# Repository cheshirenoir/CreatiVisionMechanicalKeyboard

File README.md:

CreatiVision Mechanical Keyboard
Untested (as yet. It's about $100 in parts!)
CC BY SA
Made in KiCAD

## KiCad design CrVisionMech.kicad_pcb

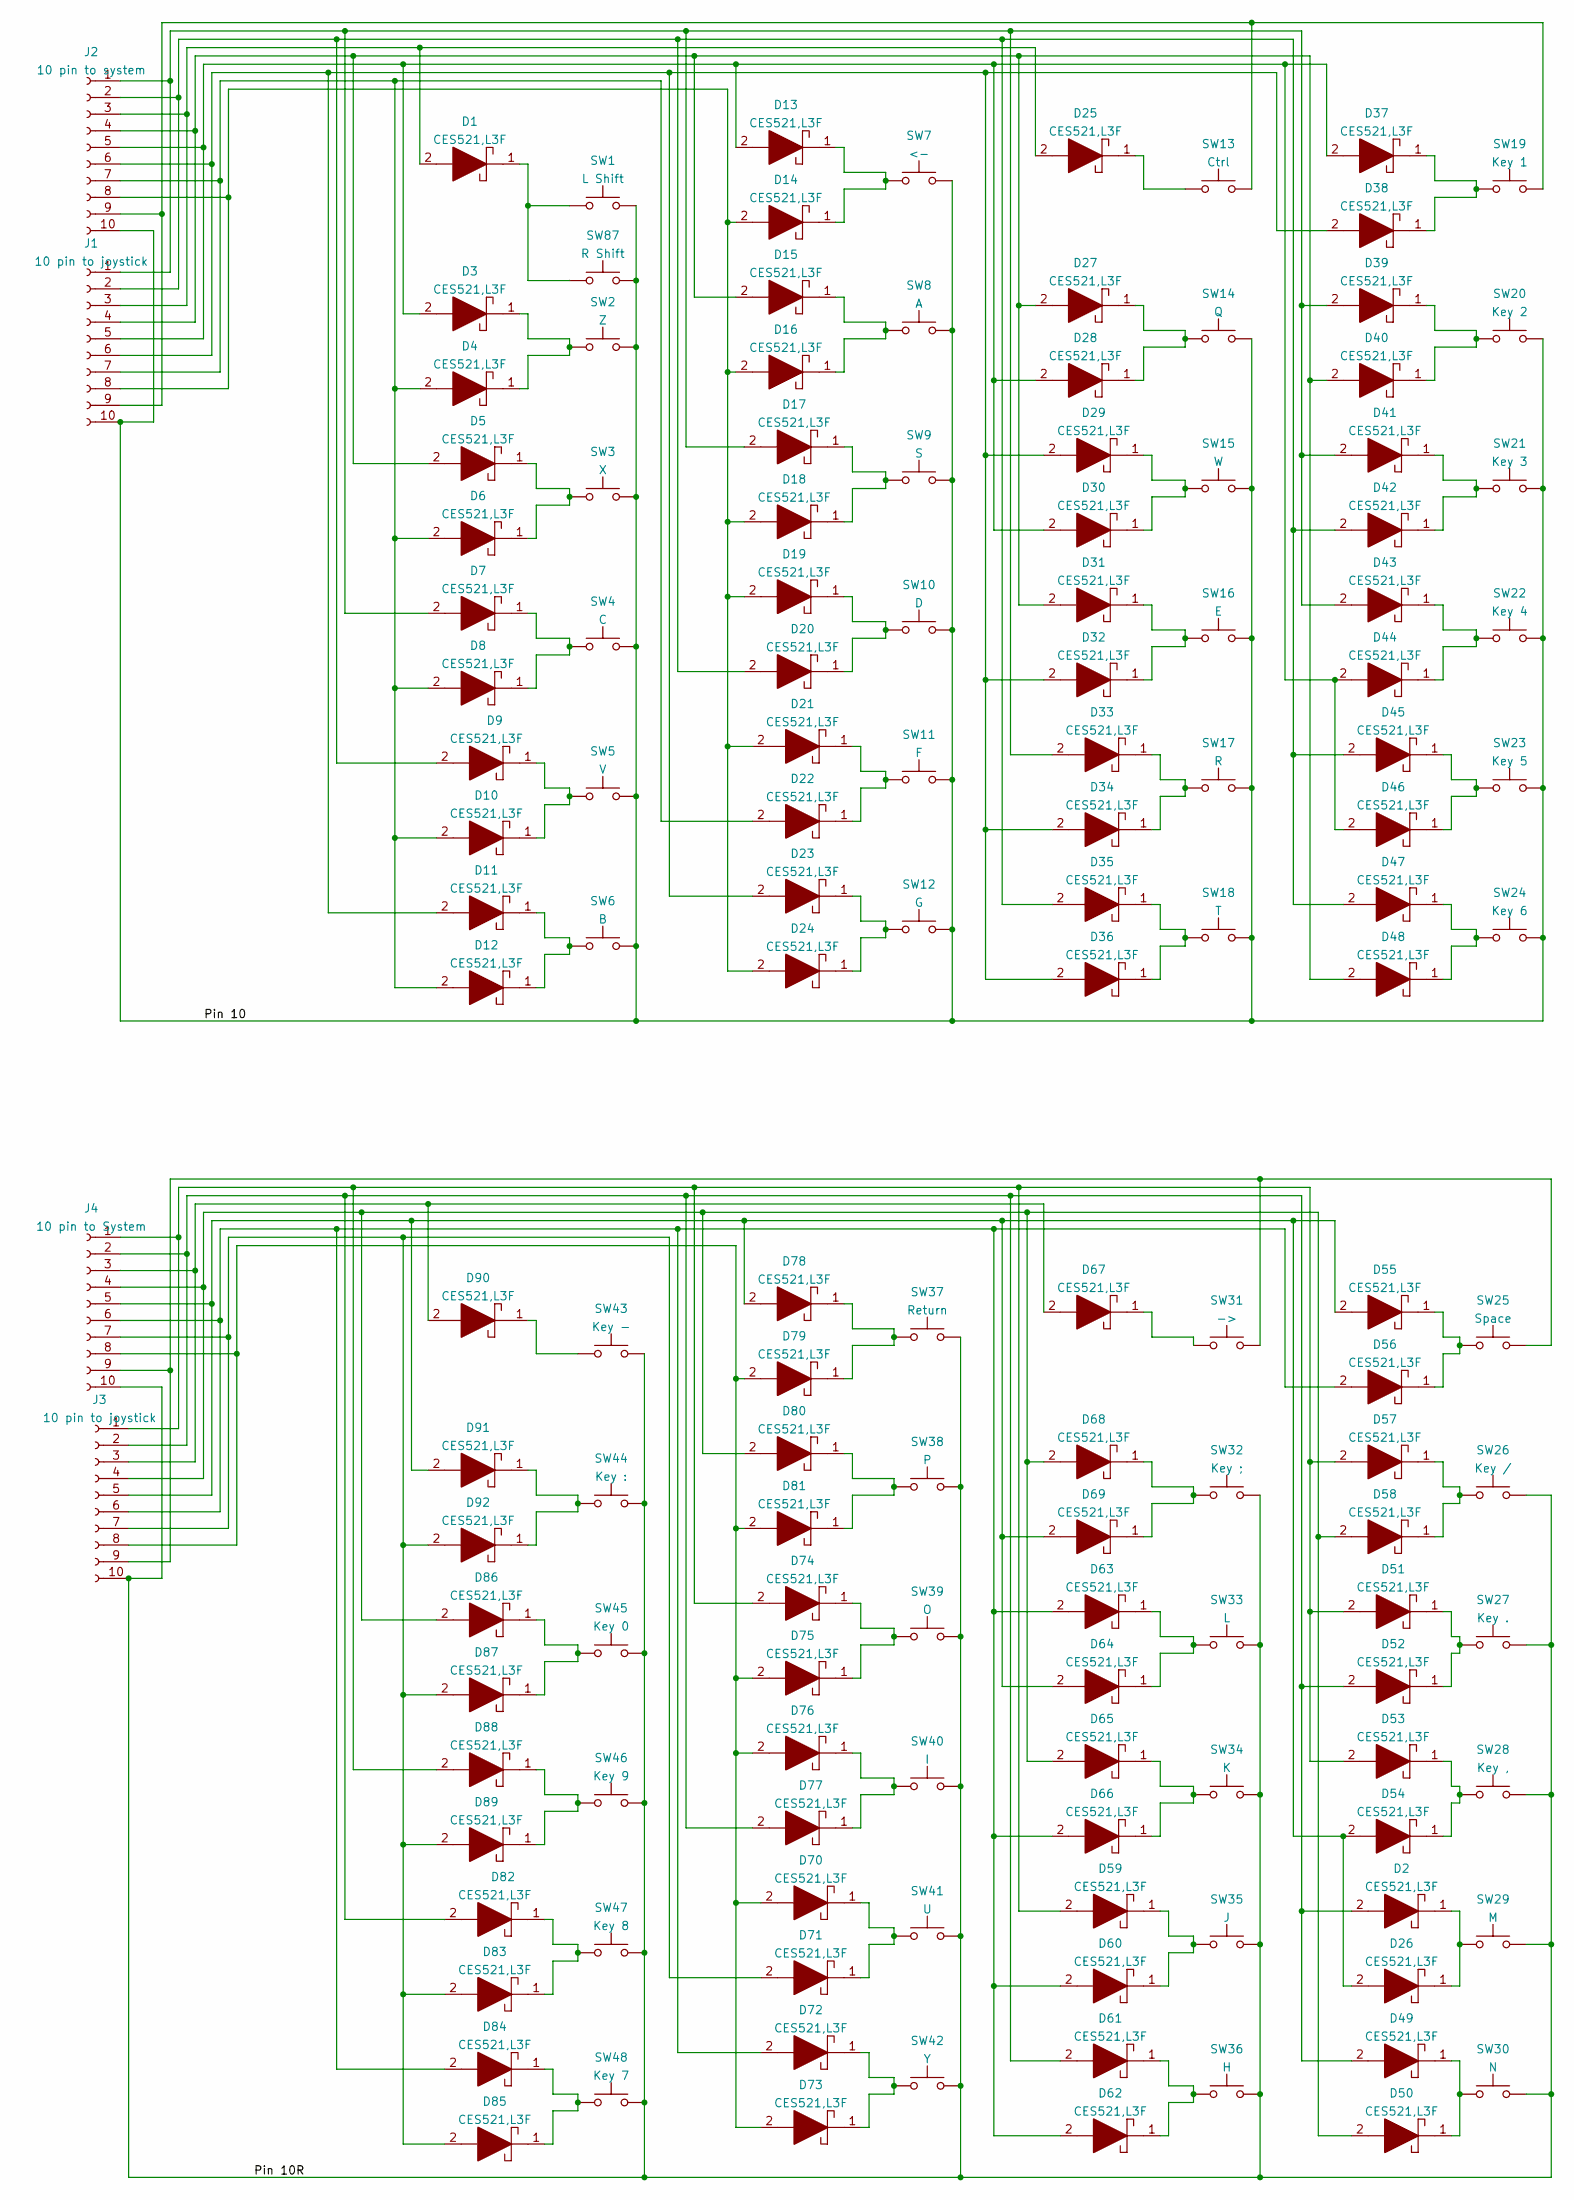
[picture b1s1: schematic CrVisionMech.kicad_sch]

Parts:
D1, D2, D3, D4, D5, D6, D7, D8, D9, D10, D11, D12, D13, D14, D15, D16, D17, D18, D19, D20, D21, D22, D23, D24, D25, D26, D27, D28, D29, D30, D31, D32, D33, D34, D35, D36, D37, D38, D39, D40, D41, D42, D43, D44, D45, D46, D47, D48, D49, D50, D51, D52, D53, D54, D55, D56, D57, D58, D59, D60, D61, D62, D63, D64, D65, D66, D67, D68, D69, D70, D71, D72, D73, D74, D75, D76, D77, D78, D79, D80, D81, D82, D83, D84, D85, D86, D87, D88, D89, D90, D91, D92: CES521,L3F; D_SOD-523; Manufacturer_Part_Number CES521,L3F; Mouser Part Number 757-CES521L3F
J1, J3: 10 pin to joystick; PinHeader_1x10_P2.54mm_Vertical
J2: 10 pin to system; PinHeader_1x10_P2.54mm_Vertical
J4: 10 pin to System; PinHeader_1x10_P2.54mm_Vertical
SW1: L Shift; SW_Cherry_MX_2.25u_PCB
SW2: Z; SW_Cherry_MX_1.00u_PCB
SW3: X; SW_Cherry_MX_1.00u_PCB
SW4: C; SW_Cherry_MX_1.00u_PCB
SW5: V; SW_Cherry_MX_1.00u_PCB
SW6: B; SW_Cherry_MX_1.00u_PCB
SW7: <-; SW_Cherry_MX_1.00u_PCB
SW8: A; SW_Cherry_MX_1.00u_PCB
SW9: S; SW_Cherry_MX_1.00u_PCB
SW10: D; SW_Cherry_MX_1.00u_PCB
SW11: F; SW_Cherry_MX_1.00u_PCB
SW12: G; SW_Cherry_MX_1.00u_PCB
SW13: Ctrl; SW_Cherry_MX_1.25u_PCB
SW14: Q; SW_Cherry_MX_1.00u_PCB
SW15: W; SW_Cherry_MX_1.00u_PCB
SW16: E; SW_Cherry_MX_1.00u_PCB
SW17: R; SW_Cherry_MX_1.00u_PCB
SW18: T; SW_Cherry_MX_1.00u_PCB
SW19: Key 1; SW_Cherry_MX_1.00u_PCB
SW20: Key 2; SW_Cherry_MX_1.00u_PCB
SW21: Key 3; SW_Cherry_MX_1.00u_PCB
SW22: Key 4; SW_Cherry_MX_1.00u_PCB
SW23: Key 5; SW_Cherry_MX_1.00u_PCB
SW24: Key 6; SW_Cherry_MX_1.00u_PCB
SW25: Space; SW_Cherry_MX_6.25u_PCB
SW26: Key /; SW_Cherry_MX_1.00u_PCB
SW27: Key .; SW_Cherry_MX_1.00u_PCB
SW28: Key ,; SW_Cherry_MX_1.00u_PCB
SW29: M; SW_Cherry_MX_1.00u_PCB
SW30: N; SW_Cherry_MX_1.00u_PCB
SW31: ->; SW_Cherry_MX_1.00u_PCB
SW32: Key ;; SW_Cherry_MX_1.00u_PCB
SW33: L; SW_Cherry_MX_1.00u_PCB
SW34: K; SW_Cherry_MX_1.00u_PCB
SW35: J; SW_Cherry_MX_1.00u_PCB
SW36: H; SW_Cherry_MX_1.00u_PCB
SW37: Return; SW_Cherry_MX_2.25u_PCB
SW38: P; SW_Cherry_MX_1.00u_PCB
SW39: O; SW_Cherry_MX_1.00u_PCB
SW40: I; SW_Cherry_MX_1.00u_PCB
SW41: U; SW_Cherry_MX_1.00u_PCB
SW42: Y; SW_Cherry_MX_1.00u_PCB
SW43: Key -; SW_Cherry_MX_1.00u_PCB
SW44: Key :; SW_Cherry_MX_1.00u_PCB
SW45: Key 0; SW_Cherry_MX_1.00u_PCB
SW46: Key 9; SW_Cherry_MX_1.00u_PCB
SW47: Key 8; SW_Cherry_MX_1.00u_PCB
SW48: Key 7; SW_Cherry_MX_1.00u_PCB
SW87: R Shift; SW_Cherry_MX_2.25u_PCB

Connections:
/Pin 10: J1.10, J2.10, SW1.2, SW2.2, SW3.2, SW4.2, SW5.2, SW6.2, SW7.2, SW8.2, SW9.2, SW10.2, SW11.2, SW12.2, SW14.2, SW15.2, SW16.2, SW17.2, SW18.2, SW20.2, SW21.2, SW22.2, SW23.2, SW24.2, SW87.2
/Pin 10R: J3.10, J4.10, SW26.1, SW27.1, SW28.1, SW29.1, SW30.1, SW32.1, SW33.1, SW34.1, SW35.1, SW36.1, SW37.1, SW38.1, SW39.1, SW40.1, SW41.1, SW42.1, SW43.1, SW44.1, SW45.1, SW46.1, SW47.1, SW48.1
unnamed: D1.1, SW1.1, SW87.1
unnamed: D1.2, D25.2, J1.3, J2.3
unnamed: D2.1, D26.1, SW29.2
unnamed: D2.2, D49.2, D52.2, D61.2, D77.2, D82.2, J3.2, J4.2
unnamed: D3.1, D4.1, SW2.1
unnamed: D5.1, D6.1, SW3.1
unnamed: D7.1, D8.1, SW4.1
unnamed: D9.1, D10.1, SW5.1
unnamed: D4.2, D6.2, D8.2, D10.2, D12.2, D22.2, J1.7, J2.7
unnamed: D11.1, D12.1, SW6.1
unnamed: D11.2, D23.2, D29.2, D32.2, D34.2, D36.2, D38.2, J1.6, J2.6
unnamed: D13.1, D14.1, SW7.1
unnamed: D3.2, D13.2, D28.2, D30.2, D37.2, D44.2, D46.2, J1.5, J2.5
unnamed: D14.2, D16.2, D18.2, D19.2, D21.2, D24.2, J1.8, J2.8
unnamed: D15.1, D16.1, SW8.1
unnamed: D5.2, D15.2, D27.2, D31.2, D40.2, D48.2, J1.4, J2.4
unnamed: D17.1, D18.1, SW9.1
unnamed: D7.2, D17.2, D33.2, D39.2, D41.2, D43.2, J1.1, J2.1
unnamed: D19.1, D20.1, SW10.1
unnamed: D9.2, D20.2, D35.2, D42.2, D45.2, D47.2, J1.2, J2.2
unnamed: D21.1, D22.1, SW11.1
unnamed: D23.1, D24.1, SW12.1
unnamed: D25.1, SW13.1
unnamed: D26.2, D54.2, D55.2, D64.2, D69.2, D78.2, D91.2, J3.5, J4.5
unnamed: D27.1, D28.1, SW14.1
unnamed: D29.1, D30.1, SW15.1
unnamed: D31.1, D32.1, SW16.1
unnamed: D33.1, D34.1, SW17.1
unnamed: D35.1, D36.1, SW18.1
unnamed: D37.1, D38.1, SW19.1
unnamed: D39.1, D40.1, SW20.1
unnamed: D41.1, D42.1, SW21.1
unnamed: D43.1, D44.1, SW22.1
unnamed: D45.1, D46.1, SW23.1
unnamed: D47.1, D48.1, SW24.1
unnamed: D49.1, D50.1, SW30.2
unnamed: D50.2, D58.2, D65.2, D68.2, D80.2, D86.2, J3.4, J4.4
unnamed: D51.1, D52.1, SW27.2
unnamed: D51.2, D53.2, D57.2, D59.2, D74.2, D88.2, J3.1, J4.1
unnamed: D53.1, D54.1, SW28.2
unnamed: D55.1, D56.1, SW25.2
unnamed: D56.2, D60.2, D62.2, D63.2, D66.2, D72.2, D84.2, J3.6, J4.6
unnamed: D57.1, D58.1, SW26.2
unnamed: D59.1, D60.1, SW35.2
unnamed: D61.1, D62.1, SW36.2
unnamed: D63.1, D64.1, SW33.2
unnamed: D65.1, D66.1, SW34.2
unnamed: D67.1, SW31.2
unnamed: D67.2, D90.2, J3.3, J4.3
unnamed: D68.1, D69.1, SW32.2
unnamed: D70.1, D71.1, SW41.2
unnamed: D70.2, D73.2, D75.2, D76.2, D79.2, D81.2, J3.8, J4.8
unnamed: D71.2, D83.2, D85.2, D87.2, D89.2, D92.2, J3.7, J4.7
unnamed: D72.1, D73.1, SW42.2
unnamed: D74.1, D75.1, SW39.2
unnamed: D76.1, D77.1, SW40.2
unnamed: D78.1, D79.1, SW37.2
unnamed: D80.1, D81.1, SW38.2
unnamed: D82.1, D83.1, SW47.2
unnamed: D84.1, D85.1, SW48.2
unnamed: D86.1, D87.1, SW45.2
unnamed: D88.1, D89.1, SW46.2
unnamed: D90.1, SW43.2
unnamed: D91.1, D92.1, SW44.2
unnamed: J1.9, J2.9, SW13.2, SW19.2
unnamed: J3.9, J4.9, SW25.1, SW31.1

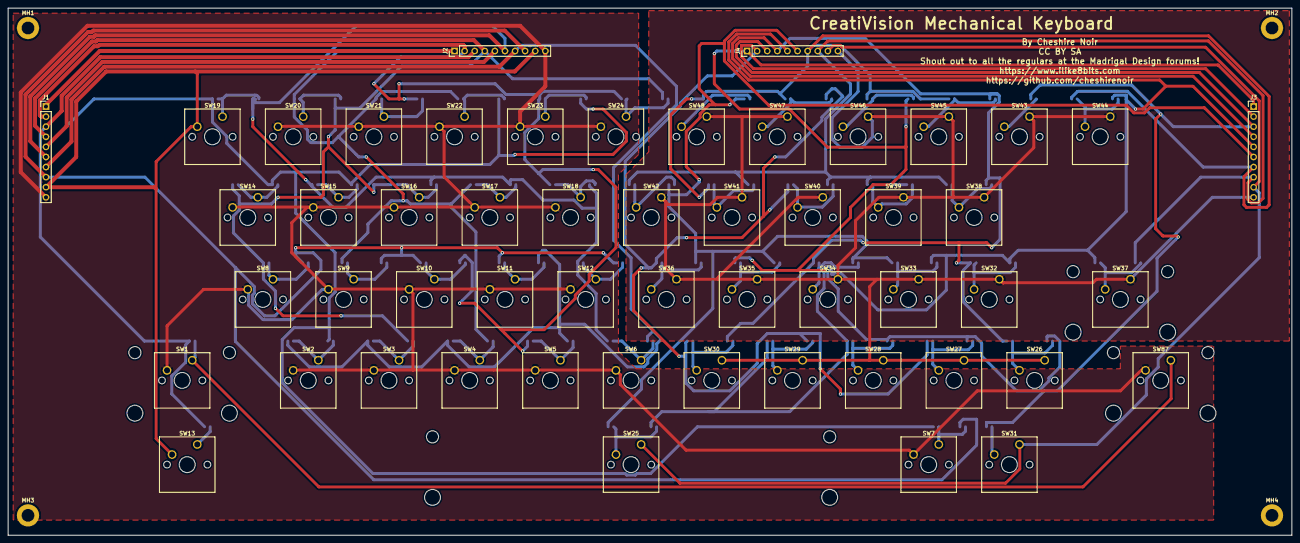
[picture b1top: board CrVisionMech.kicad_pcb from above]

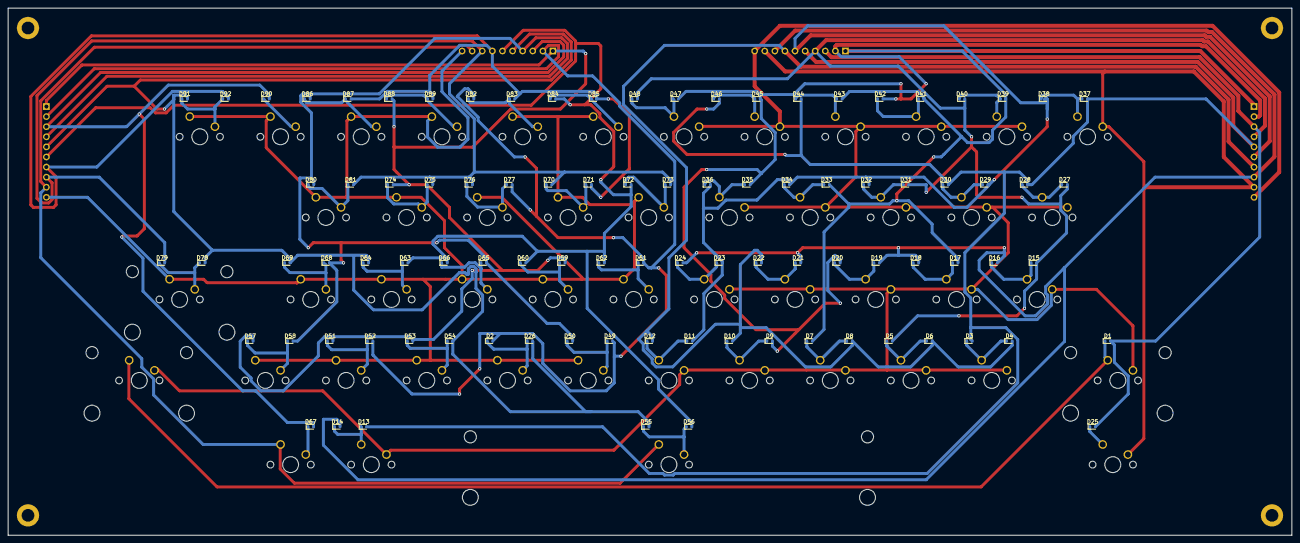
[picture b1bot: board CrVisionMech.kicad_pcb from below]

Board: 2 copper layers, 323.2 x 132.7 mm, 149 parts (92 on the bottom side), 68 nets.

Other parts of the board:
MH1, MH2, MH3, MH4: MountingHole_3.2mm_M3_DIN965_Pad
